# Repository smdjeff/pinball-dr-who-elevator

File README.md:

# dr-who

Replacement elevator mechanism for the Dr Who pinball machine. 

https://en.wikipedia.org/wiki/Doctor_Who_(pinball)

https://youtu.be/fHkql48IPpg

https://youtu.be/L-MsUkgBwkI

<table><tr>
<td rowspan="2"></td>
<td rowspan="2"></td>
</tr>
<tr><td></td></tr>
</table>

## Firmware
* Drop in replacement to original system
* Uses simulated cam stimulus into factory system
* Passes factory diagnostics tests 

## Electronics
* Custom electronics
* Drop in replacement for bi-directional motor board A-15782
* Modern current limiting for saftey
* Modern acceleration and deceleration profiles for smooth start and stop

## Mechanical
* Custom brackets - laser cut and bent
* Standard desktop CNC stepper motor, rod, and nut.
* Replaces original parts
  * Cam A-15035
  * Motor 14-7970
  * Bracket A-15037
  * Support Bracket A-15036
  * Roller 02-4764

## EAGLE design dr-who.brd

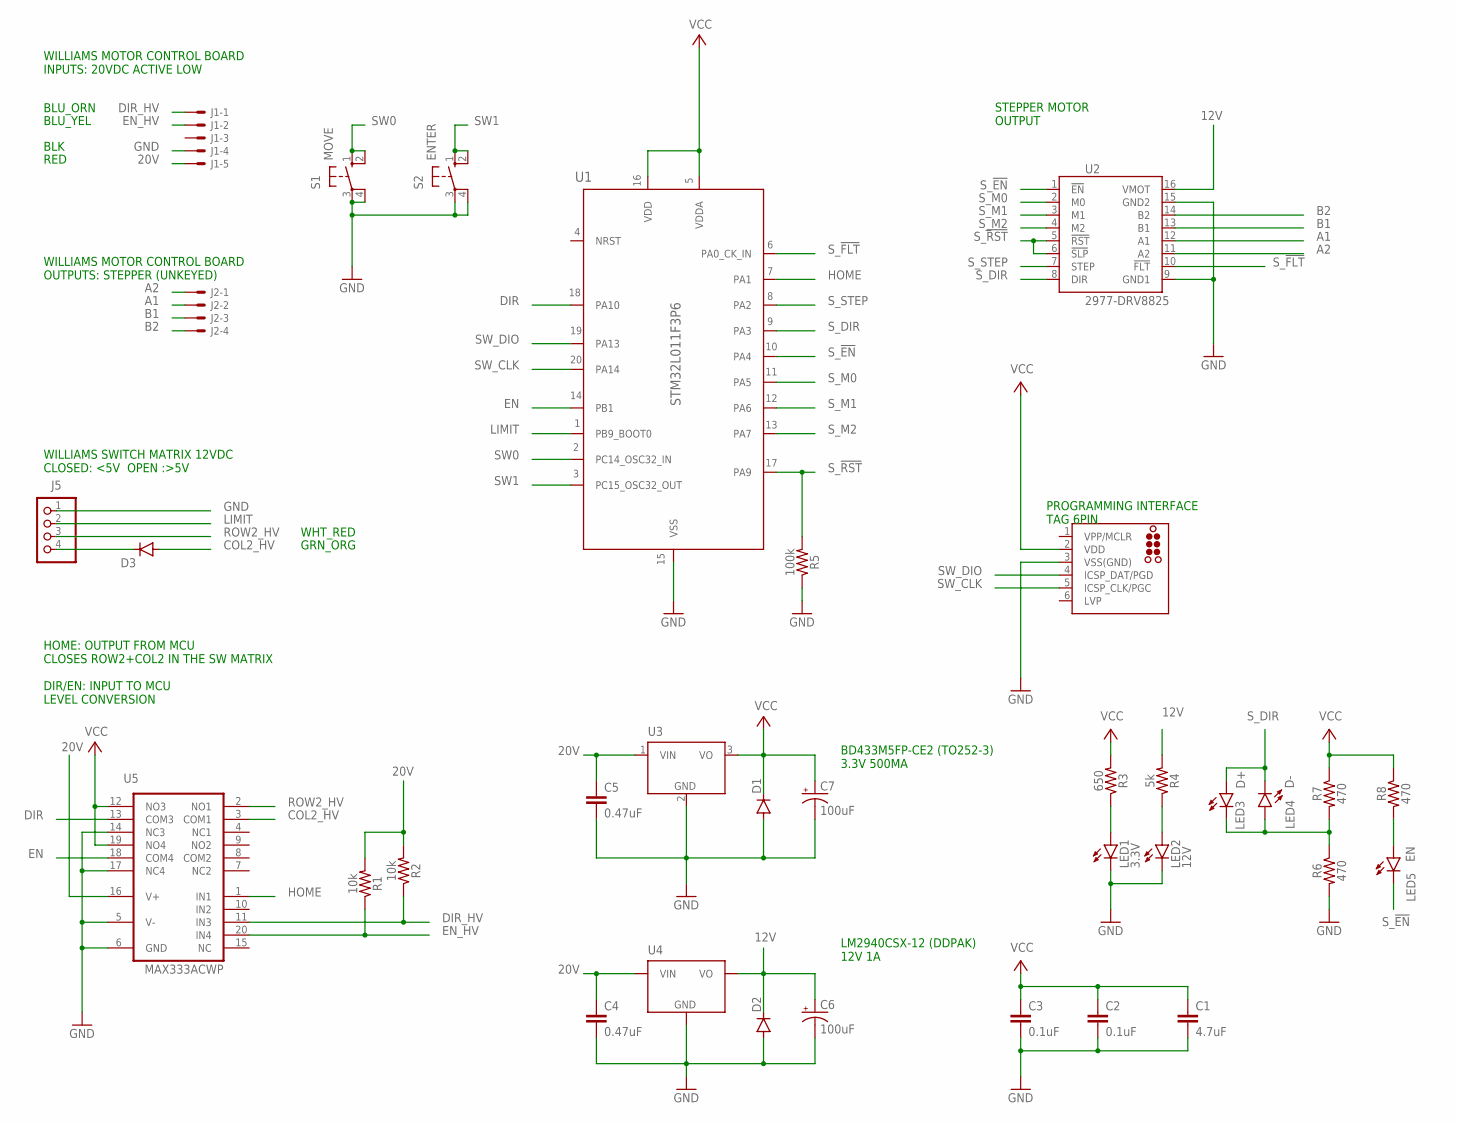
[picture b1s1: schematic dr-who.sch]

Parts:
C1: 4.7uF; 0603
C2, C3: 0.1uF; 0603
C4, C5: 0.47uF; 0603
C6, C7: 100uF; CPOL-RADIAL-2.5MM-6.5MM
D1, D2, D3: DIODE-SOD323-R; SOD323-R
J1: KK-156-5
J2: KK-156-4
J4: TC2030-MCP-NL
J5: PINHD-1X4; 1X04
LED1: 3.3V; LED3MM
LED2: 12V; LED3MM
LED3: D+; LED3MM
LED4: D-; LED3MM
LED5: EN; LED3MM
R1, R2: 10k; 0603
R3: 650; 0603
R4: 5k; 0603
R5: 100k; 0603
R6, R7, R8: 470; 0603
S1: MOVE; B3F/40XX
S2: ENTER; B3F/40XX
U1: STM32L011F3P6; TSSOP20-I
U2: 2977-DRV8825; DRV8825
U3: LM2936DT-3.3; TO252; MPN BD433M5FP-CE2
U4: LM2936D2PAK; D2PAK
U5: MAX333ACWP; SO20L

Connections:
12V: C6.1 (+), D2.C, R4.2, U2.16 (VMOT), U4.3 (VO)
20V: C4.1, C5.1, J1.5, R1.2, R2.2, U3.1 (VIN), U4.1 (VIN), U5.16 (V+)
A1: J2.2, U2.12 (A1)
A2: J2.1, U2.11 (A2)
B1: J2.3, U2.13 (B1)
B2: J2.4, U2.14 (B2)
COL2_HV: D3.A, U5.3 (COM1)
DIR: U1.18 (PA10), U5.13 (COM3)
DIR_HV: J1.1, R2.1, U5.11 (IN3)
EN: U1.14 (PB1), U5.18 (COM4)
EN_HV: J1.2, R1.1, U5.20 (IN4)
GND: C1.2, C2.2, C3.2, C4.2, C5.2, C6.2 (-), C7.2 (-), D1.A, D2.A, J1.4, J4.3 (VSS(GND)), J5.1, LED1.K (C), LED2.K (C), R5.1, R6.2, S1.3, S1.4 (P1), S2.3, S2.4 (P1), U1.15 (VSS), U2.9 (GND1), U2.15 (GND2), U3.2 (GND), U4.2 (GND), U5.5 (V-), U5.6 (GND), U5.14 (NC3), U5.17 (NC4)
HOME: U1.7 (PA1), U5.1 (IN1)
LIMIT: J5.2, U1.1 (PB9_BOOT0)
unnamed: D3.C, J5.4
unnamed: LED3.K (C), LED4.A, R6.1, R7.2
unnamed: LED5.A, R8.2
unnamed: LED1.A, R3.1
unnamed: LED2.A, R4.1
ROW2_HV: J5.3, U5.2 (NO1)
SW0: S1.1 (S), S1.2 (S1), U1.2 (PC14_OSC32_IN)
SW1: S2.1 (S), S2.2 (S1), U1.3 (PC15_OSC32_OUT)
SW_CLK: J4.5 (ICSP_CLK/PGC), U1.20 (PA14)
SW_DIO: J4.4 (ICSP_DAT/PGD), U1.19 (PA13)
S_!EN: LED5.K (C), U1.10 (PA4), U2.1 (!EN)
S_!FLT: U1.6 (PA0_CK_IN), U2.10 (!FLT)
S_!RST: R5.2, U1.17 (PA9), U2.5 (!RST), U2.6 (!SLP)
S_DIR: LED3.A, LED4.K (C), U1.9 (PA3), U2.8 (DIR)
S_M0: U1.11 (PA5), U2.2 (M0)
S_M1: U1.12 (PA6), U2.3 (M1)
S_M2: U1.13 (PA7), U2.4 (M2)
S_STEP: U1.8 (PA2), U2.7 (STEP)
VCC: C1.1, C2.1, C3.1, C7.1 (+), D1.C, J4.2 (VDD), R3.2, R7.1, R8.1, U1.5 (VDDA), U1.16 (VDD), U3.3 (VO), U5.12 (NO3), U5.19 (NO4)

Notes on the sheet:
BLU_ORN
BLU_YEL
RED
BLK
LM2940CSX-12 (DDPAK) 12V 1A
BD433M5FP-CE2 (TO252-3) 3.3V 500MA
WILLIAMS MOTOR CONTROL BOARD INPUTS: 20VDC ACTIVE LOW
PROGRAMMING INTERFACE TAG 6PIN
WHT_RED
GRN_ORG
WILLIAMS SWITCH MATRIX 12VDC CLOSED: <5V OPEN :>5V
STEPPER MOTOR OUTPUT
WILLIAMS MOTOR CONTROL BOARD OUTPUTS: STEPPER (UNKEYED)
HOME: OUTPUT FROM MCU CLOSES ROW2+COL2 IN THE SW MATRIX DIR/EN: INPUT TO MCU LEVEL CONVERSION

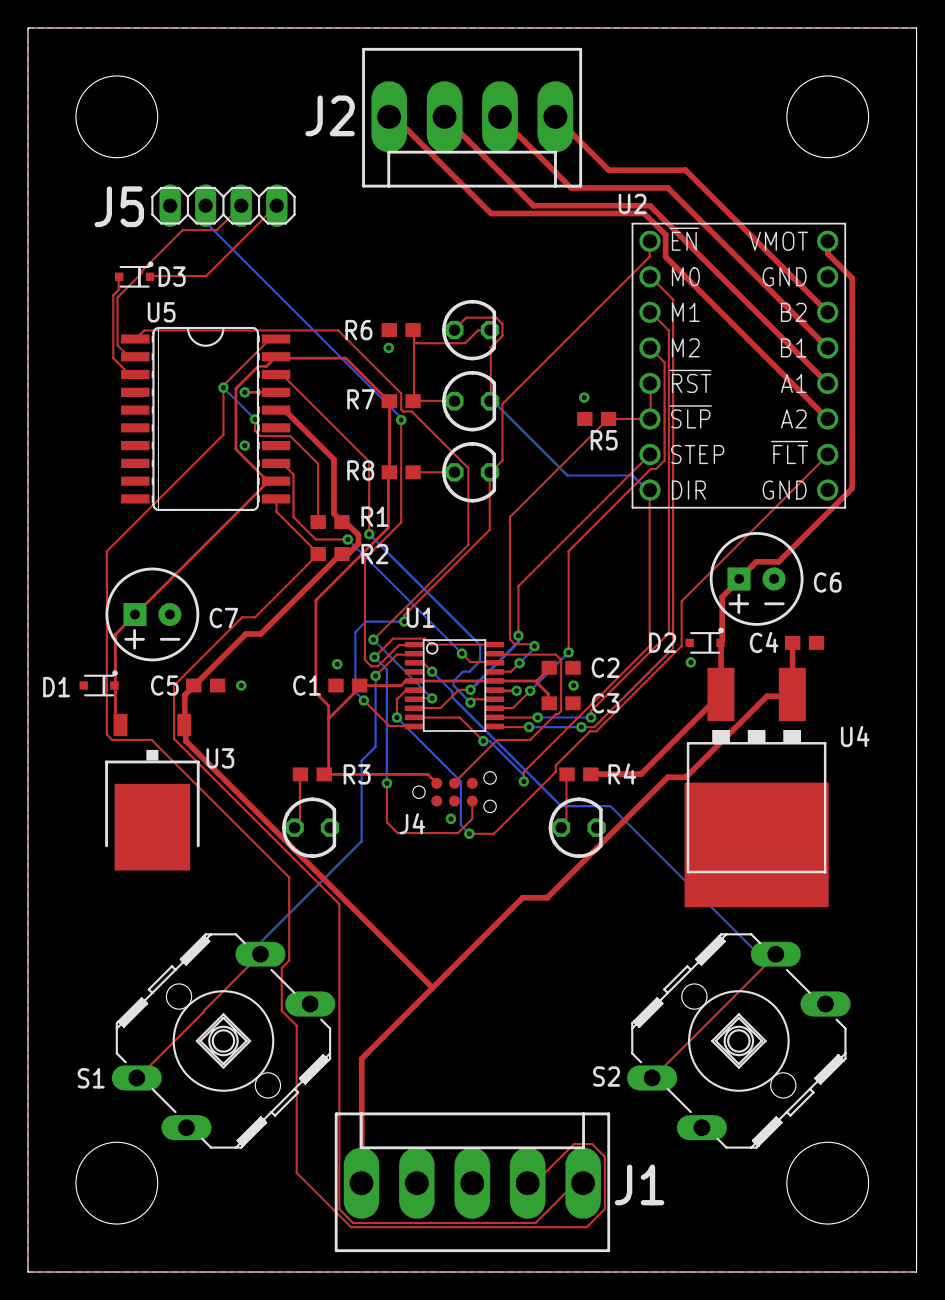
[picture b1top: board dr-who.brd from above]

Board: 2 copper layers, 63.5 x 88.9 mm, 34 parts (0 on the bottom side), 33 nets.

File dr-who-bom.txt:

Partlist exported from /Users/jmathews/Documents/EAGLE/projects/dr-who.sch at 5/8/21 1:46 PM

Part Value         Device                           Package                 Description                                                               MF    MPN           OC_FARNELL OC_NEWARK POPULARITY PROD_ID   VALUE
C1   4.7uF         4.7UF0603                        0603                    4.7µF ceramic capacitors                                                                                                      CAP-08280 4.7uF
C2   0.1uF         0.1UF-0603-25V-(+80/-20%)        0603                    0.1µF ceramic capacitors                                                                                                      CAP-00810 0.1uF
C3   0.1uF         0.1UF-0603-25V-(+80/-20%)        0603                    0.1µF ceramic capacitors                                                                                                      CAP-00810 0.1uF
C4   0.47uF        470PF-0603-50V-5%                0603                    470pF ceramic capacitors                                                                                                      CAP-07884 470pF
C5   0.47uF        470PF-0603-50V-5%                0603                    470pF ceramic capacitors                                                                                                      CAP-07884 470pF
C6   100uF         100UF-POLAR-RADIAL-2.5MM-25V-20% CPOL-RADIAL-2.5MM-6.5MM 100µF polarized capacitors                                                                                                    CAP-08439 100uF
C7   100uF         100UF-POLAR-RADIAL-2.5MM-25V-20% CPOL-RADIAL-2.5MM-6.5MM 100µF polarized capacitors                                                                                                    CAP-08439 100uF
D1                 DIODE-SOD323-R                   SOD323-R                DIODE                                                                                                              4                         
D2                 DIODE-SOD323-R                   SOD323-R                DIODE                                                                                                              4                         
D3                 DIODE-SOD323-R                   SOD323-R                DIODE                                                                                                              4                         
J1                 KK-156-5                         KK-156-5                KK 156 HEADER                                                             MOLEX               unknown    unknown   0                         
J2                 KK-156-4                         KK-156-4                KK 156 HEADER                                                             MOLEX               unknown    unknown   0                         
J4                 TC2030-MCP-NL                    TC2030-MCP-NL           TAG-CONNECT ICSP ConnectorManufacturer: Tag-Connect                                                                                          
J5                 PINHD-1X4                        1X04                    PIN HEADER                                                                                                         91                        
LED1 3.3V          LED3MM                           LED3MM                  LED                                                                                                                97                        
LED2 12V           LED3MM                           LED3MM                  LED                                                                                                                97                        
LED3 D+            LED3MM                           LED3MM                  LED                                                                                                                97                        
LED4 D-            LED3MM                           LED3MM                  LED                                                                                                                97                        
LED5 EN            LED3MM                           LED3MM                  LED                                                                                                                97                        
R1   10k           10KOHM-0603-1/10W-1%             0603                    10kΩ resistor                                                                                                                 RES-00824 10k  
R2   10k           10KOHM-0603-1/10W-1%             0603                    10kΩ resistor                                                                                                                 RES-00824 10k  
R3   650           10KOHM-0603-1/10W-1%             0603                    10kΩ resistor                                                                                                                 RES-00824 10k  
R4   5k            10KOHM-0603-1/10W-1%             0603                    10kΩ resistor                                                                                                                 RES-00824 10k  
R5   100k          10KOHM-0603-1/10W-1%             0603                    10kΩ resistor                                                                                                                 RES-00824 10k  
R6   470           10KOHM-0603-1/10W-1%             0603                    10kΩ resistor                                                                                                                 RES-00824 10k  
R7   470           10KOHM-0603-1/10W-1%             0603                    10kΩ resistor                                                                                                                 RES-00824 10k  
R8   470           10KOHM-0603-1/10W-1%             0603                    10kΩ resistor                                                                                                                 RES-00824 10k  
S1   MOVE          40/XX                            B3F/40XX                OMRON SWITCH                                                                                  unknown    unknown   0                         
S2   ENTER         40/XX                            B3F/40XX                OMRON SWITCH                                                                                  unknown    unknown   0                         
U1   STM32L011F3P6 STM32L011F3P6                    TSSOP20-I               IC                                                                                                                                           
U2   2977-DRV8825  2977-DRV8825                     DRV8825                 DRV8825 Stepper Motor Driver Carrier; High Current (Bulk; No Header Pins)                                                                    
U3   LM2936DT-3.3  LM2936DT-3.3                     TO252                   Ultra-Low Quiescent Current LDO Voltage Regulator                               BD433M5FP-CE2 1286863    26M0361   0                         
U4   LM2936D2PAK   LM2936D2PAK                      D2PAK                   Ultra-Low Quiescent Current LDO Voltage Regulator                                                                                            
U5   MAX333ACWP    MAX333ACWP                       SO20L                   ANALOG SWITCH                                                             MAXIM MAX333ACWP+   9725547    28K3302   0

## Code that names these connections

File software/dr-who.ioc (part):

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Mcu.Name=STM32L011F(3-4)Px
Mcu.Package=TSSOP20
Mcu.UserName=STM32L011F3Px
PA0-CK_IN.GPIOParameters=GPIO_PuPd,GPIO_Label,GPIO_ModeDefaultEXTI
PA0-CK_IN.GPIO_Label=S_NFLT
PA0-CK_IN.GPIO_ModeDefaultEXTI=GPIO_MODE_IT_FALLING
PA0-CK_IN.GPIO_PuPd=GPIO_PULLUP
PA0-CK_IN.Signal=GPXTI0
PA1.GPIOParameters=GPIO_Label
PA1.GPIO_Label=HOME
PA1.Signal=GPIO_Output
PA10.GPIOParameters=GPIO_Label
PA10.GPIO_Label=DIR
PA10.Signal=GPIO_Input
PA13.Mode=Serial_Wire
PA13.Signal=SYS_SWDIO
PA14.Mode=Serial_Wire
PA14.Signal=SYS_SWCLK
PA2.GPIOParameters=GPIO_Label
PA2.GPIO_Label=S_STEP
PA2.Signal=GPIO_Output
PA3.GPIOParameters=GPIO_Label
PA3.GPIO_Label=S_DIR
PA3.Signal=GPIO_Output
PA4.GPIOParameters=GPIO_Label
PA4.GPIO_Label=S_NEN
PA4.Signal=GPIO_Output
PA5.GPIOParameters=GPIO_Label
PA5.GPIO_Label=S_M0
PA5.Signal=GPIO_Output
PA6.GPIOParameters=GPIO_Label
PA6.GPIO_Label=S_M1
PA6.Signal=GPIO_Output
PA7.GPIOParameters=GPIO_Label
PA7.GPIO_Label=S_M2
PA7.Signal=GPIO_Output
PA9.GPIOParameters=GPIO_Speed,GPIO_Label
PA9.GPIO_Label=S_NRST
PA9.GPIO_Speed=GPIO_SPEED_FREQ_LOW
PA9.Signal=GPIO_Output
PB1.GPIOParameters=GPIO_Label
PB1.GPIO_Label=EN
PB1.Signal=GPIO_Input
PB9-BOOT0.GPIOParameters=GPIO_PuPd,GPIO_Label,GPIO_ModeDefaultEXTI
PB9-BOOT0.GPIO_Label=LIMIT
PB9-BOOT0.GPIO_ModeDefaultEXTI=GPIO_MODE_IT_FALLING
PB9-BOOT0.GPIO_PuPd=GPIO_PULLUP
PB9-BOOT0.Signal=GPXTI9
PC14-OSC32_IN.GPIOParameters=GPIO_PuPd,GPIO_Label
PC14-OSC32_IN.GPIO_Label=SW0
PC14-OSC32_IN.GPIO_PuPd=GPIO_PULLUP
PC14-OSC32_IN.Signal=GPIO_Input
PC15-OSC32_OUT.GPIOParameters=GPIO_PuPd,GPIO_Label
PC15-OSC32_OUT.GPIO_Label=SW1
PC15-OSC32_OUT.GPIO_PuPd=GPIO_PULLUP
PC15-OSC32_OUT.Signal=GPIO_Input
RCC.HSE_VALUE=8000000
RCC.SYSCLKFreq_VALUE=32000000
RCC.SYSCLKSource=RCC_SYSCLKSOURCE_PLLCLK
board=custom

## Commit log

2021-05-09 no message
2021-05-09 stm32-mx for makefile (not stm32-ide)
2021-05-09 weird.
2021-05-13 very first pass at setting things up
2021-05-14 move from hal to ll so this thing actually builds in 8k flash
2021-05-25 get systick working
2021-05-26 set reset pin correctly.
2021-05-26 attempt at stepper acceleration
2021-06-02 get it working again.
2021-06-06 improved opto home output. inactivity timer.
2021-06-06 move from degrees to level based system.
2021-06-07 passing test!
2021-06-18 it's generally working
2021-06-26 add nv storage for step adjustment. disable inactivity timer.
2021-07-06 add mechanical drawings

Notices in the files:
parts and their libraries:
SparkFun-Capacitors: Licensing: Creative Commons ShareAlike 4.0 International - https://creativecommons.org/licenses/by-sa/4.0
tag-connect: ©2009 ROFA.cz - modified and updated by Robert Darlington ‹rdarlington@gmail.com›
